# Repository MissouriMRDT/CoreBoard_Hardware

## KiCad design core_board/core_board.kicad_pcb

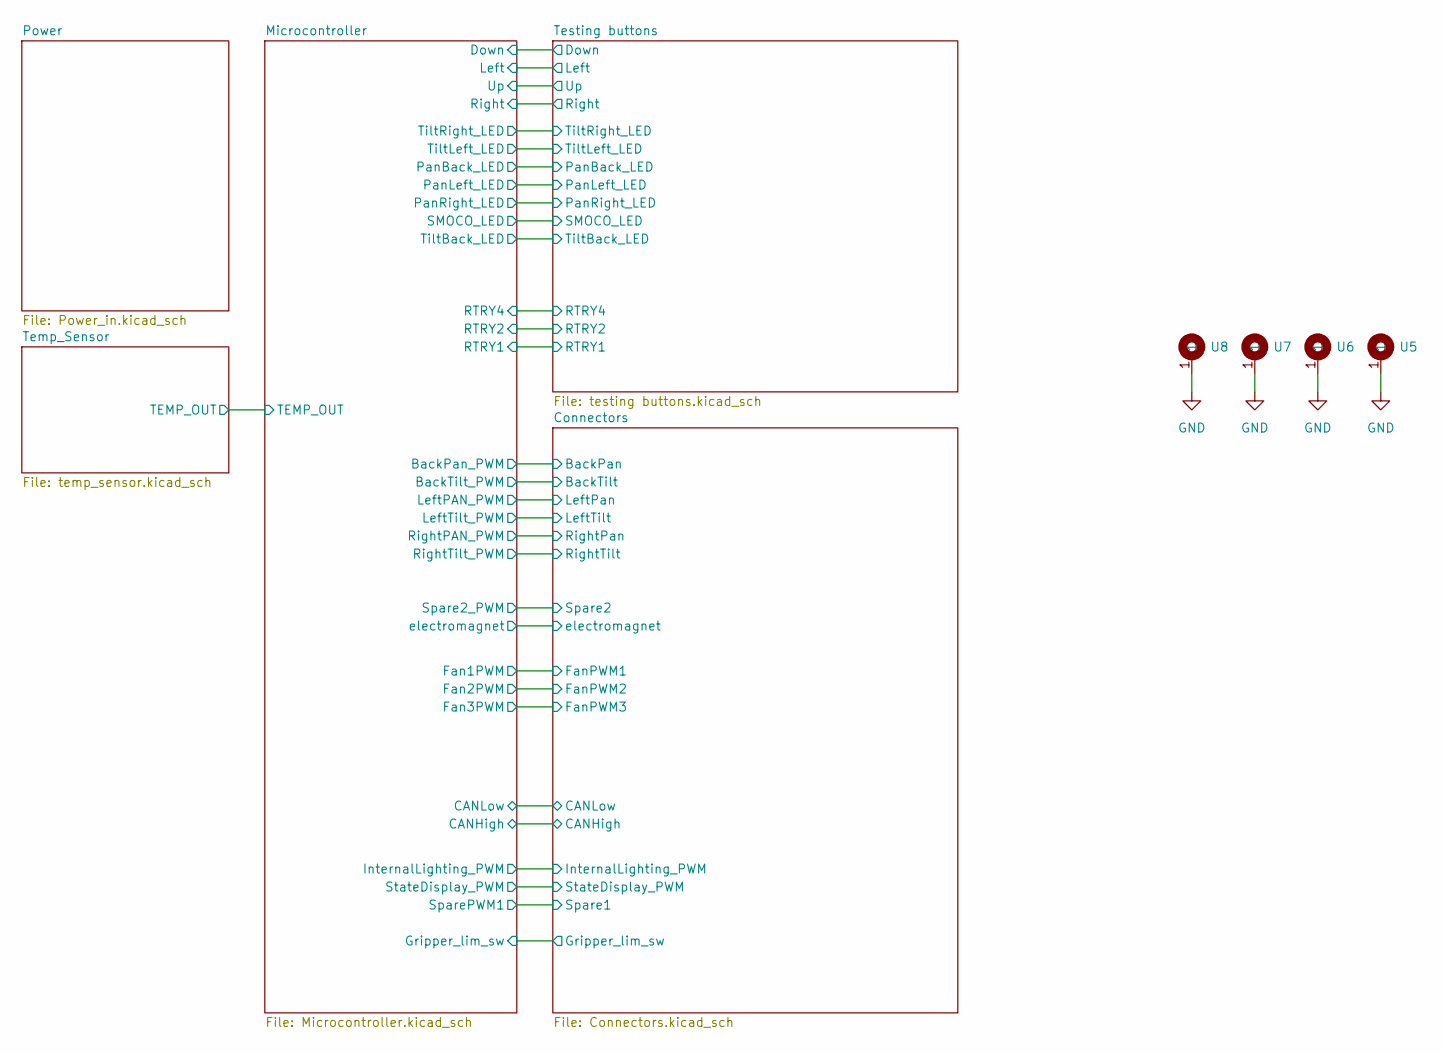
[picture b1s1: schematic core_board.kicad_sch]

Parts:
U5, U6, U7, U8: 4_40_Hole_Pad_Via

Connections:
GND: U5.1 (1_1), U6.1 (1_1), U7.1 (1_1), U8.1 (1_1); also elsewhere on the board

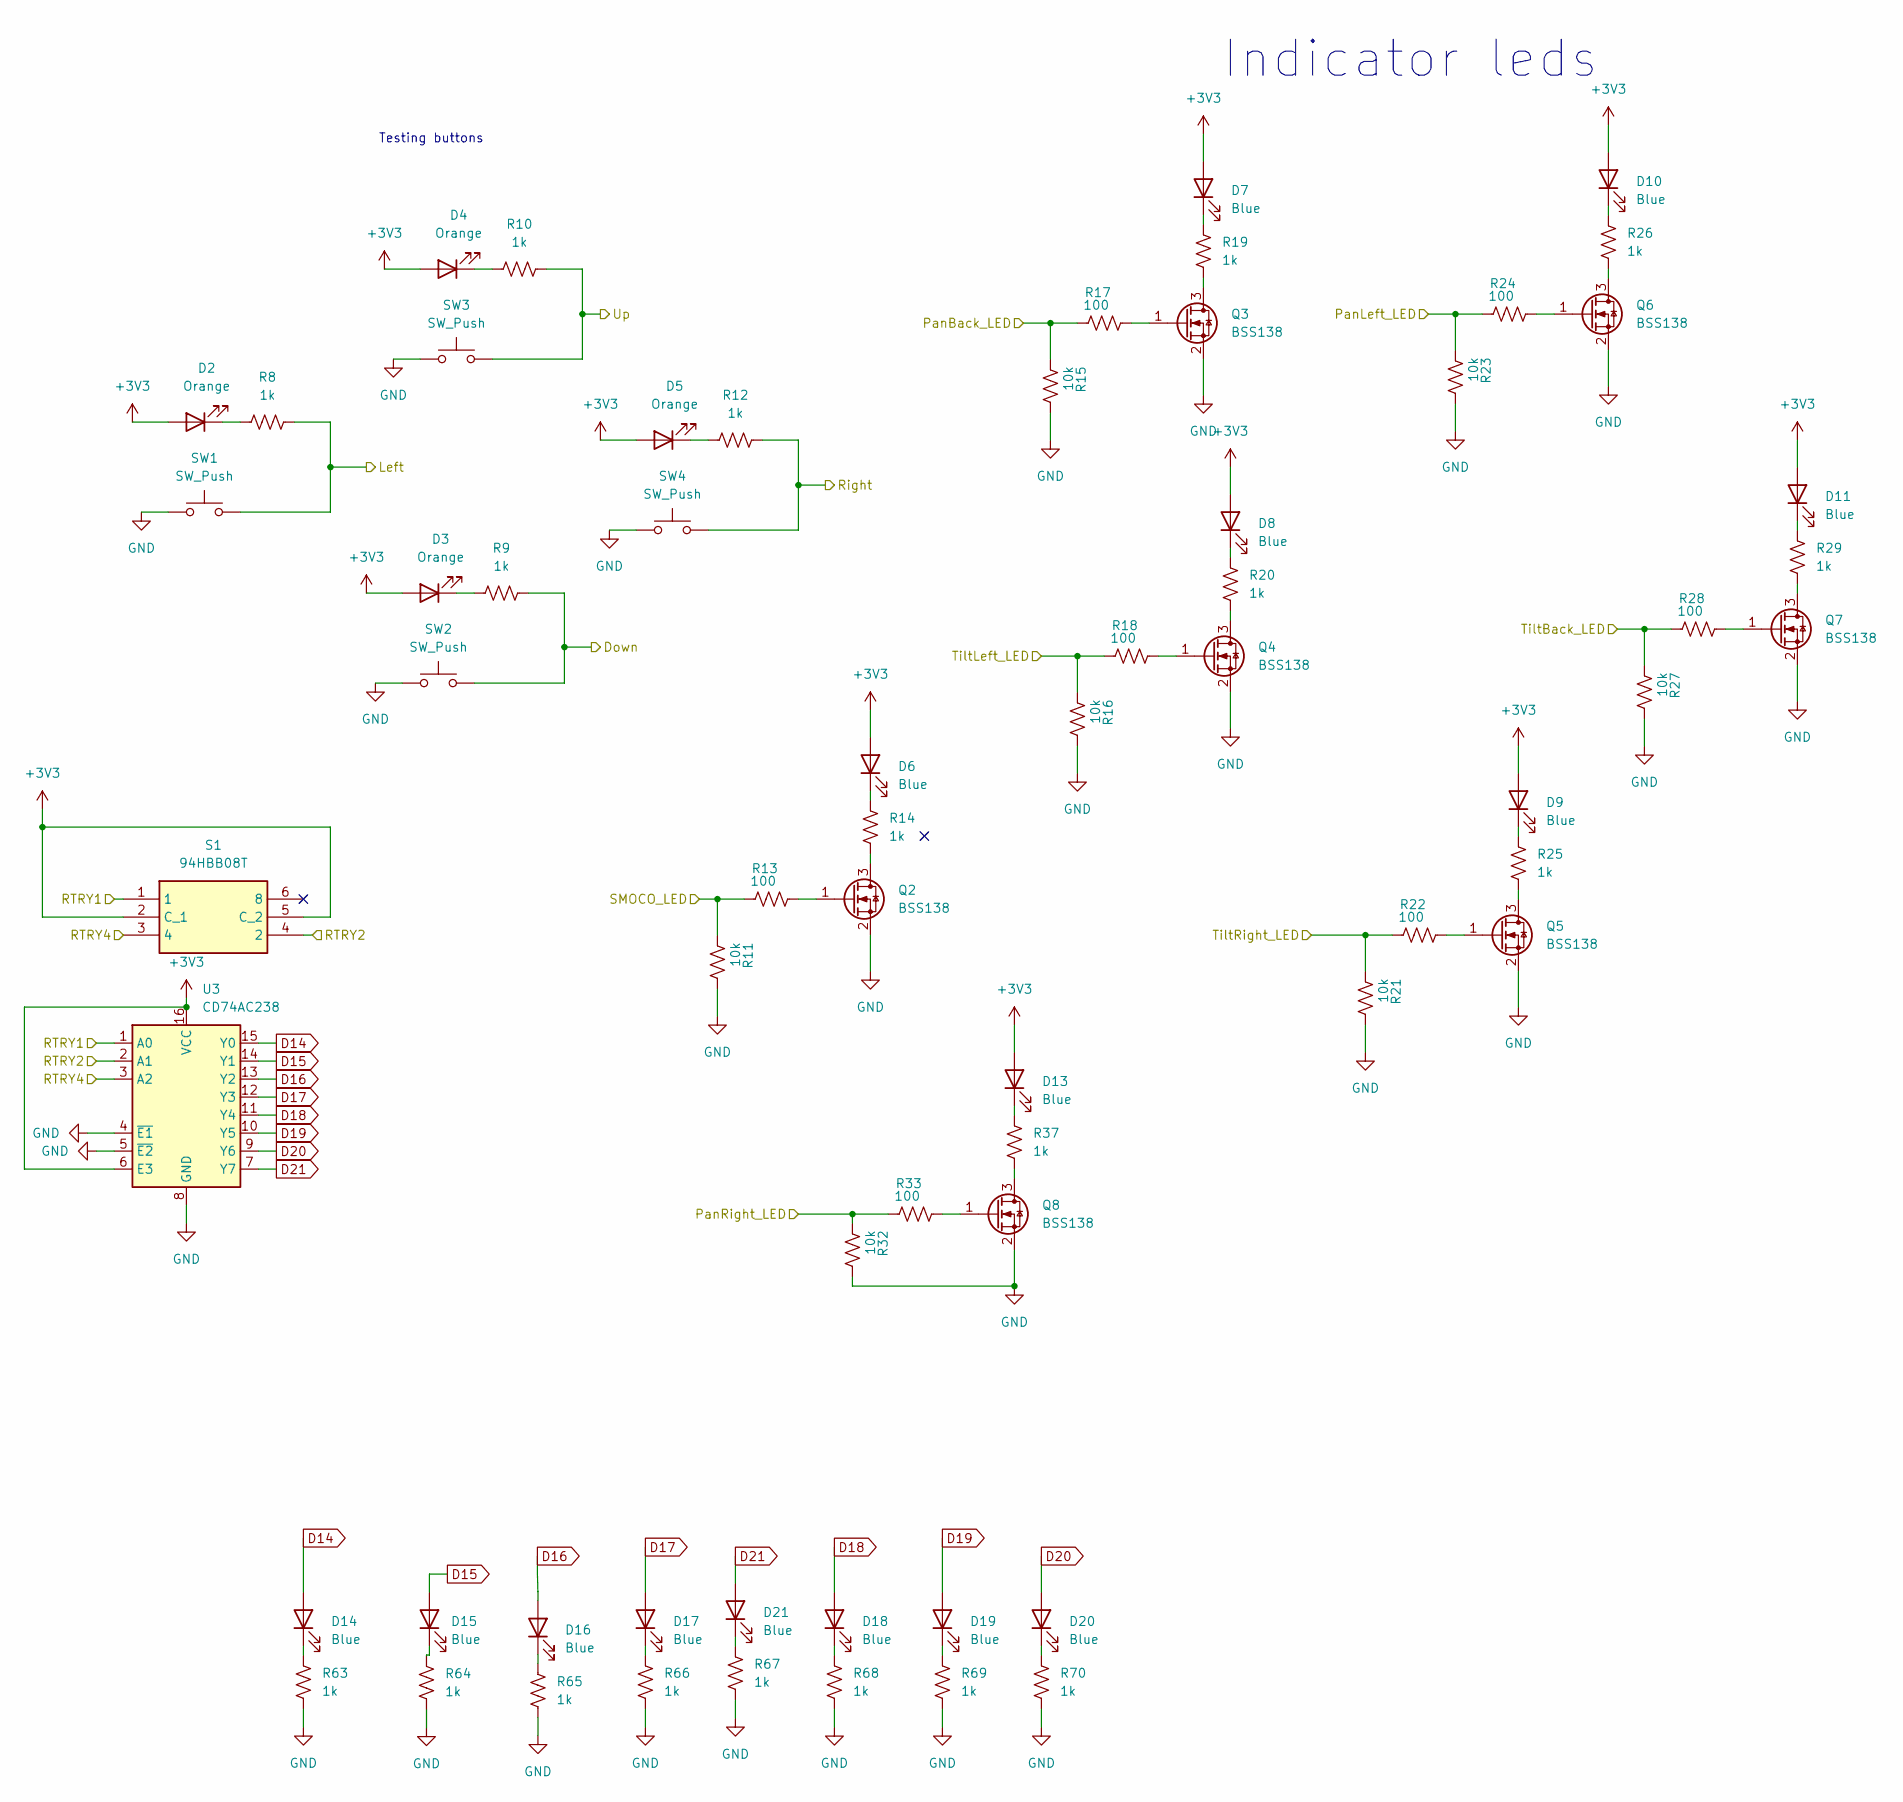
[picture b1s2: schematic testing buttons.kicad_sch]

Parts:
D2, D3, D4, D5: Orange; LED_0603_1608Metric_Pad1.05x0.95mm_HandSolder
D6, D7, D8, D9, D10, D11, D13, D14, D15, D16, D17, D18, D19, D20, D21: Blue; LED_0603_1608Metric_Pad1.05x0.95mm_HandSolder
Q2, Q3, Q4, Q5, Q6, Q7, Q8: BSS138; SOT-23
R8, R9, R10, R12, R14, R19, R20, R25, R26, R29, R37, R63, R64, R65, R66, R67, R68, R69, R70: 1k; R_0603_1608Metric_Pad0.98x0.95mm_HandSolder
R11, R15, R16, R21, R23, R27, R32: 10k; R_0603_1608Metric_Pad0.98x0.95mm_HandSolder
R13, R17, R18, R22, R24, R28, R33: 100; R_0603_1608Metric_Pad0.98x0.95mm_HandSolder
S1: 94HBB08T; DIPS762W56P254L991H597Q6N; Manufacturer_Part_Number 94HBB08T; Mouser Part Number 706-94HBB08T
SW1, SW2, SW3, SW4: SW_Push; SW_SPST_TL3305A
U3: CD74AC238; TSSOP-16_4.4x5mm_P0.65mm

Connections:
+3V3: D2.2 (A), D3.2 (A), D4.2 (A), D5.2 (A), D6.2 (A), D7.2 (A), D8.2 (A), D9.2 (A), D10.2 (A), D11.2 (A), D13.2 (A), S1.2 (C_1), S1.5 (C_2), U3.6 (E3), U3.16 (VCC); also elsewhere on the board
/Microcontroller/Down: R9.1, SW2.2; also elsewhere on the board
/Microcontroller/Left: R8.1, SW1.2; also elsewhere on the board
/Microcontroller/PanBack_LED: R15.1, R17.1; also elsewhere on the board
/Microcontroller/PanLeft_LED: R23.1, R24.1; also elsewhere on the board
/Microcontroller/PanRight_LED: R32.1, R33.1; also elsewhere on the board
/Microcontroller/RTRY1: S1.1, U3.1 (A0); also elsewhere on the board
/Microcontroller/RTRY2: S1.4 (2), U3.2 (A1); also elsewhere on the board
/Microcontroller/RTRY4: S1.3 (4), U3.3 (A2); also elsewhere on the board
/Microcontroller/Right: R12.1, SW4.2; also elsewhere on the board
/Microcontroller/SMOCO_LED: R11.1, R13.1; also elsewhere on the board
/Microcontroller/TiltBack_LED: R27.1, R28.1; also elsewhere on the board
/Microcontroller/TiltLeft_LED: R16.1, R18.1; also elsewhere on the board
/Microcontroller/TiltRight_LED: R21.1, R22.1; also elsewhere on the board
/Microcontroller/Up: R10.1, SW3.2; also elsewhere on the board
D14: D14.2 (A), U3.15 (Y0)
D15: D15.2 (A), U3.14 (Y1)
D16: D16.2 (A), U3.13 (Y2)
D17: D17.2 (A), U3.12 (Y3)
D18: D18.2 (A), U3.11 (Y4)
D19: D19.2 (A), U3.10 (Y5)
D20: D20.2 (A), U3.9 (Y6)
D21: D21.2 (A), U3.7 (Y7)
GND: Q2.2 (S), Q3.2 (S), Q4.2 (S), Q5.2 (S), Q6.2 (S), Q7.2 (S), Q8.2 (S), R11.2, R15.2, R16.2, R21.2, R23.2, R27.2, R32.2, R63.2, R64.2, R65.2, R66.2, R67.2, R68.2, R69.2, R70.2, SW1.1, SW2.1, SW3.1, SW4.1, U3.4 (~E1), U3.5 (~E2), U3.8 (GND); also elsewhere on the board
unnamed: D2.1 (K), R8.2
unnamed: D3.1 (K), R9.2
unnamed: D4.1 (K), R10.2
unnamed: D5.1 (K), R12.2
unnamed: D6.1 (K), R14.1
unnamed: D7.1 (K), R19.1
unnamed: D8.1 (K), R20.1
unnamed: D9.1 (K), R25.1
unnamed: D10.1 (K), R26.1
unnamed: D11.1 (K), R29.1
unnamed: D13.1 (K), R37.1
unnamed: D14.1 (K), R63.1
unnamed: D15.1 (K), R64.1
unnamed: D16.1 (K), R65.1
unnamed: D17.1 (K), R66.1
unnamed: D18.1 (K), R68.1
unnamed: D19.1 (K), R69.1
unnamed: D20.1 (K), R70.1
unnamed: D21.1 (K), R67.1
unnamed: Q2.3 (D), R14.2
unnamed: Q2.1 (G), R13.2
unnamed: Q3.3 (D), R19.2
unnamed: Q3.1 (G), R17.2
unnamed: Q4.3 (D), R20.2
unnamed: Q4.1 (G), R18.2
unnamed: Q5.3 (D), R25.2
unnamed: Q5.1 (G), R22.2
unnamed: Q6.3 (D), R26.2
unnamed: Q6.1 (G), R24.2
unnamed: Q7.3 (D), R29.2
unnamed: Q7.1 (G), R28.2
unnamed: Q8.3 (D), R37.2
unnamed: Q8.1 (G), R33.2

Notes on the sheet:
Indicator leds
Testing buttons

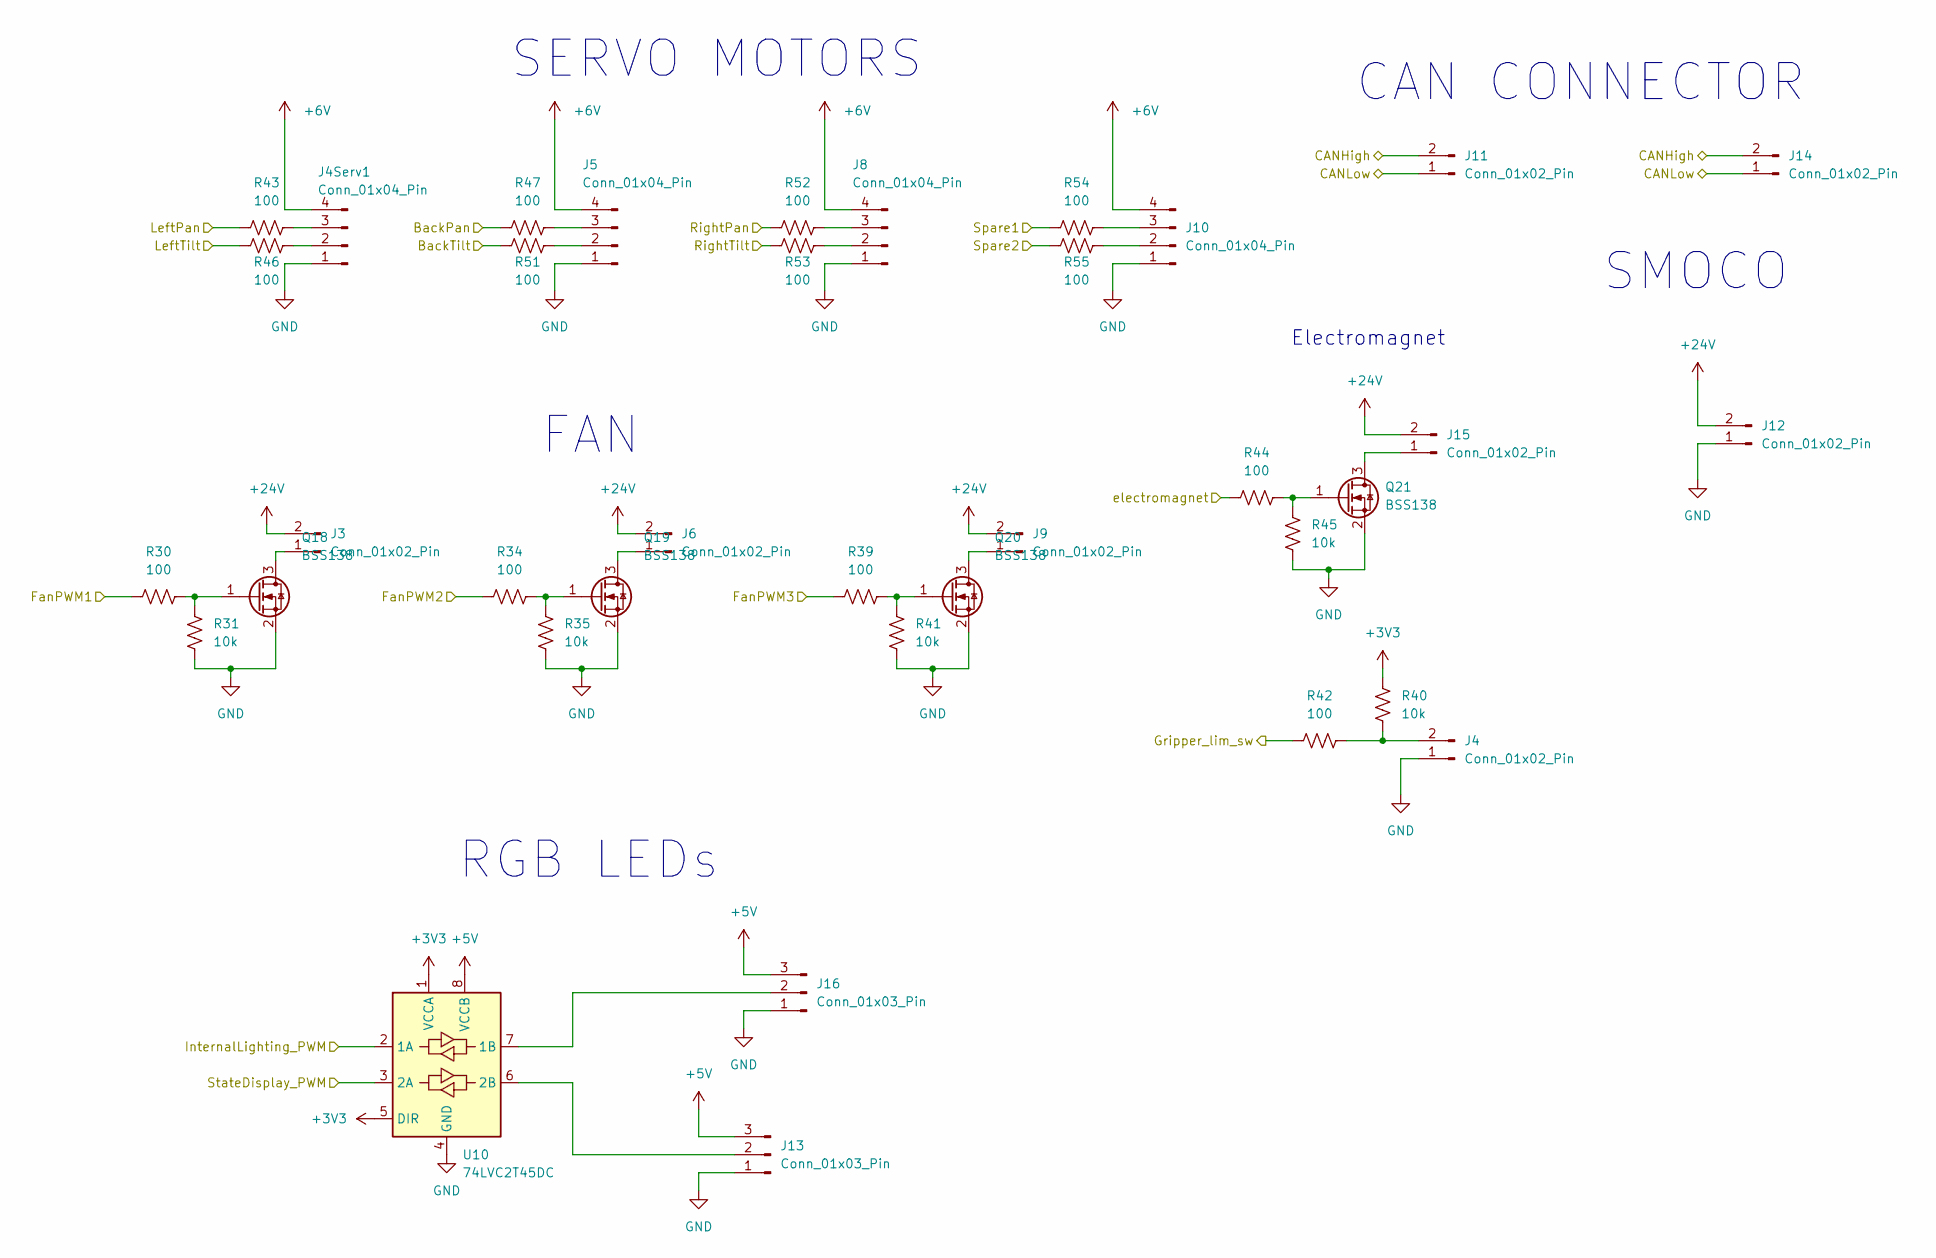
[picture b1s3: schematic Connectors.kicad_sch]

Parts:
J3, J4, J6, J9, J11, J14, J15: Conn_01x02_Pin; JST_PH_B2B-PH-K_1x02_P2.00mm_Vertical
J4Serv1, J5, J8, J10: Conn_01x04_Pin; JST_PH_B4B-PH-K_1x04_P2.00mm_Vertical
J12: Conn_01x02_Pin; MOLEX_MegaFit_02_Vertical
J13, J16: Conn_01x03_Pin; JST_PH_B3B-PH-K_1x03_P2.00mm_Vertical
Q18, Q19, Q20, Q21: BSS138; SOT-23
R30, R34, R39, R42, R43, R44, R46, R47, R51, R52, R53, R54, R55: 100; R_0603_1608Metric_Pad0.98x0.95mm_HandSolder
R31, R35, R40, R41, R45: 10k; R_0603_1608Metric_Pad0.98x0.95mm_HandSolder
U10: 74LVC2T45DC; VSSOP-8_2.3x2mm_P0.5mm

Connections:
+3V3: R40.1, U10.1 (VCCA), U10.5 (DIR); also elsewhere on the board
+5V: J13.3, J16.3, U10.8 (VCCB); also elsewhere on the board
+6V: J4Serv1.4, J5.4, J8.4, J10.4; also elsewhere on the board
+24V: J3.2, J6.2, J9.2, J12.2, J15.2; also elsewhere on the board
/Connectors/BackPan: R47.1; also elsewhere on the board
/Connectors/BackTilt: R51.1; also elsewhere on the board
/Connectors/CANHigh: J11.2, J14.2; also elsewhere on the board
/Connectors/CANLow: J11.1, J14.1; also elsewhere on the board
/Connectors/FanPWM1: R30.1; also elsewhere on the board
/Connectors/FanPWM2: R34.1; also elsewhere on the board
/Connectors/FanPWM3: R39.1; also elsewhere on the board
/Connectors/Gripper_lim_sw: R42.1; also elsewhere on the board
/Connectors/InternalLighting_PWM: U10.2 (1A); also elsewhere on the board
/Connectors/LeftPan: R43.1; also elsewhere on the board
/Connectors/LeftTilt: R46.1; also elsewhere on the board
/Connectors/RightPan: R52.1; also elsewhere on the board
/Connectors/RightTilt: R53.1; also elsewhere on the board
/Connectors/Spare1: R54.1; also elsewhere on the board
/Connectors/Spare2: R55.1; also elsewhere on the board
/Connectors/StateDisplay_PWM: U10.3 (2A); also elsewhere on the board
/Connectors/electromagnet: R44.1; also elsewhere on the board
GND: J4.1, J4Serv1.1, J5.1, J8.1, J10.1, J12.1, J13.1, J16.1, Q18.2 (S), Q19.2 (S), Q20.2 (S), Q21.2 (S), R31.1, R35.1, R41.1, R45.1, U10.4 (GND); also elsewhere on the board
unnamed: J3.1, Q18.3 (D)
unnamed: J4.2, R40.2, R42.2
unnamed: J4Serv1.2, R46.2
unnamed: J4Serv1.3, R43.2
unnamed: J5.2, R51.2
unnamed: J5.3, R47.2
unnamed: J6.1, Q19.3 (D)
unnamed: J8.2, R53.2
unnamed: J8.3, R52.2
unnamed: J9.1, Q20.3 (D)
unnamed: J10.2, R55.2
unnamed: J10.3, R54.2
unnamed: J13.2, U10.6 (2B)
unnamed: J15.1, Q21.3 (D)
unnamed: J16.2, U10.7 (1B)
unnamed: Q18.1 (G), R30.2, R31.2
unnamed: Q19.1 (G), R34.2, R35.2
unnamed: Q20.1 (G), R39.2, R41.2
unnamed: Q21.1 (G), R44.2, R45.2

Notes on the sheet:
SMOCO
Electromagnet
FAN
RGB LEDs
SERVO MOTORS
CAN CONNECTOR

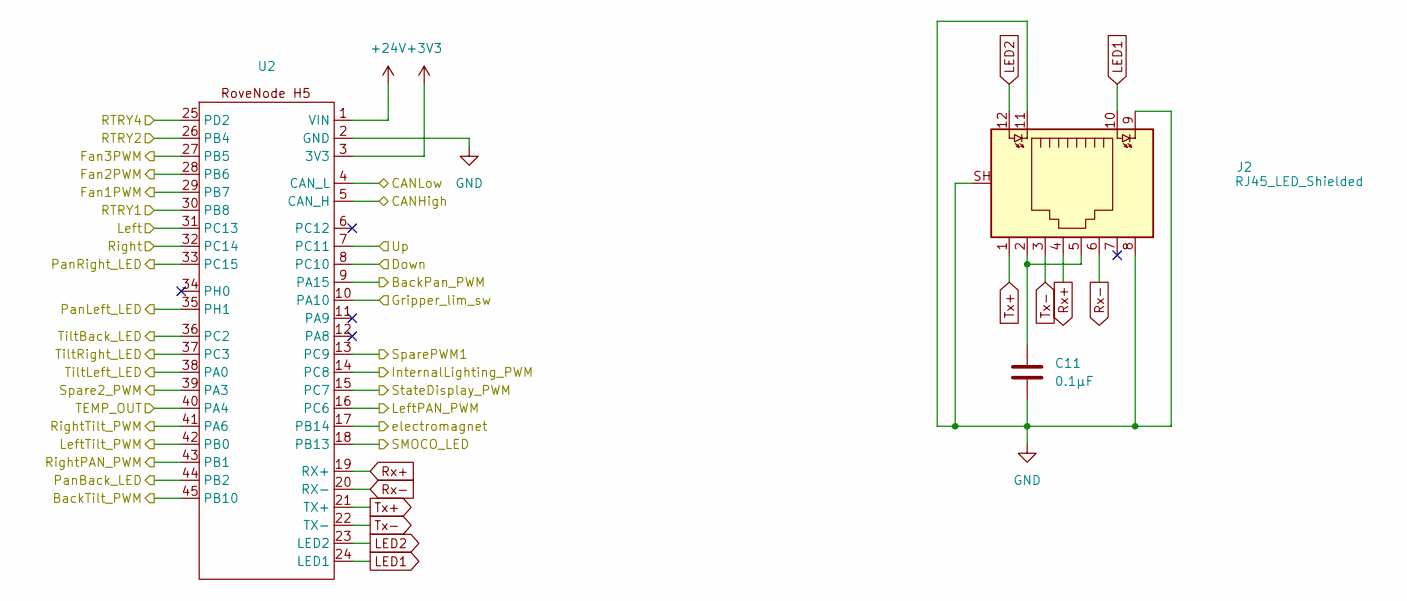
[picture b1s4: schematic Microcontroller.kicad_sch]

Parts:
C11: 0.1µF; C_0603_1608Metric_Pad1.08x0.95mm_HandSolder
J2: RJ45_LED_Shielded; RJ45_Teensy
U2: RoveNode_H5

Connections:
+3V3: U2.3 (3V3); also elsewhere on the board
+24V: U2.1 (VIN); also elsewhere on the board
/Connectors/BackPan: U2.9 (PA15); also elsewhere on the board
/Connectors/BackTilt: U2.45 (PB10); also elsewhere on the board
/Connectors/CANHigh: U2.5 (CAN_H); also elsewhere on the board
/Connectors/CANLow: U2.4 (CAN_L); also elsewhere on the board
/Connectors/FanPWM1: U2.29 (PB7); also elsewhere on the board
/Connectors/FanPWM2: U2.28 (PB6); also elsewhere on the board
/Connectors/FanPWM3: U2.27 (PB5); also elsewhere on the board
/Connectors/Gripper_lim_sw: U2.10 (PA10); also elsewhere on the board
/Connectors/InternalLighting_PWM: U2.14 (PC8); also elsewhere on the board
/Connectors/LeftPan: U2.16 (PC6); also elsewhere on the board
/Connectors/LeftTilt: U2.42 (PB0); also elsewhere on the board
/Connectors/RightPan: U2.43 (PB1); also elsewhere on the board
/Connectors/RightTilt: U2.41 (PA6); also elsewhere on the board
/Connectors/Spare1: U2.13 (PC9); also elsewhere on the board
/Connectors/Spare2: U2.39 (PA3); also elsewhere on the board
/Connectors/StateDisplay_PWM: U2.15 (PC7); also elsewhere on the board
/Connectors/electromagnet: U2.17 (PB14); also elsewhere on the board
/Microcontroller/Down: U2.8 (PC10); also elsewhere on the board
/Microcontroller/Left: U2.31 (PC13); also elsewhere on the board
/Microcontroller/PanBack_LED: U2.44 (PB2); also elsewhere on the board
/Microcontroller/PanLeft_LED: U2.35 (PH1); also elsewhere on the board
/Microcontroller/PanRight_LED: U2.33 (PC15); also elsewhere on the board
/Microcontroller/RTRY1: U2.30 (PB8); also elsewhere on the board
/Microcontroller/RTRY2: U2.26 (PB4); also elsewhere on the board
/Microcontroller/RTRY4: U2.25 (PD2); also elsewhere on the board
/Microcontroller/Right: U2.32 (PC14); also elsewhere on the board
/Microcontroller/SMOCO_LED: U2.18 (PB13); also elsewhere on the board
/Microcontroller/TEMP_OUT: U2.40 (PA4); also elsewhere on the board
/Microcontroller/TiltBack_LED: U2.36 (PC2); also elsewhere on the board
/Microcontroller/TiltLeft_LED: U2.38 (PA0); also elsewhere on the board
/Microcontroller/TiltRight_LED: U2.37 (PC3); also elsewhere on the board
/Microcontroller/Up: U2.7 (PC11); also elsewhere on the board
GND: C11.2, J2.8, J2.9, J2.11, J2.SH, U2.2 (GND); also elsewhere on the board
LED1: J2.10, U2.24 (LED1)
LED2: J2.12, U2.23 (LED2)
unnamed: C11.1, J2.2, J2.5
Rx+: J2.4, U2.19 (RX+)
Rx-: J2.6, U2.20 (RX-)
Tx+: J2.1, U2.21 (TX+)
Tx-: J2.3, U2.22 (TX-)

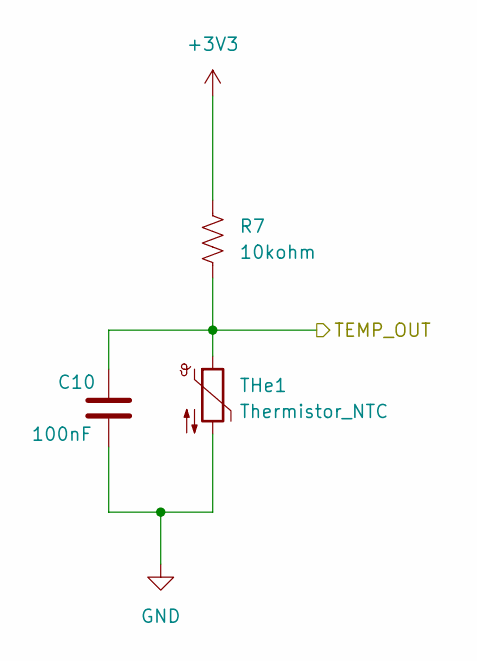
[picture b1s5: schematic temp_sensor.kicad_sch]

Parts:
C10: 100nF; C_0603_1608Metric_Pad1.08x0.95mm_HandSolder
R7: 10kohm; R_0603_1608Metric_Pad0.98x0.95mm_HandSolder
THe1: Thermistor_NTC; R_0603_1608Metric_Pad0.98x0.95mm_HandSolder

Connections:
+3V3: R7.1; also elsewhere on the board
/Microcontroller/TEMP_OUT: C10.1, R7.2, THe1.1; also elsewhere on the board
GND: C10.2, THe1.2; also elsewhere on the board

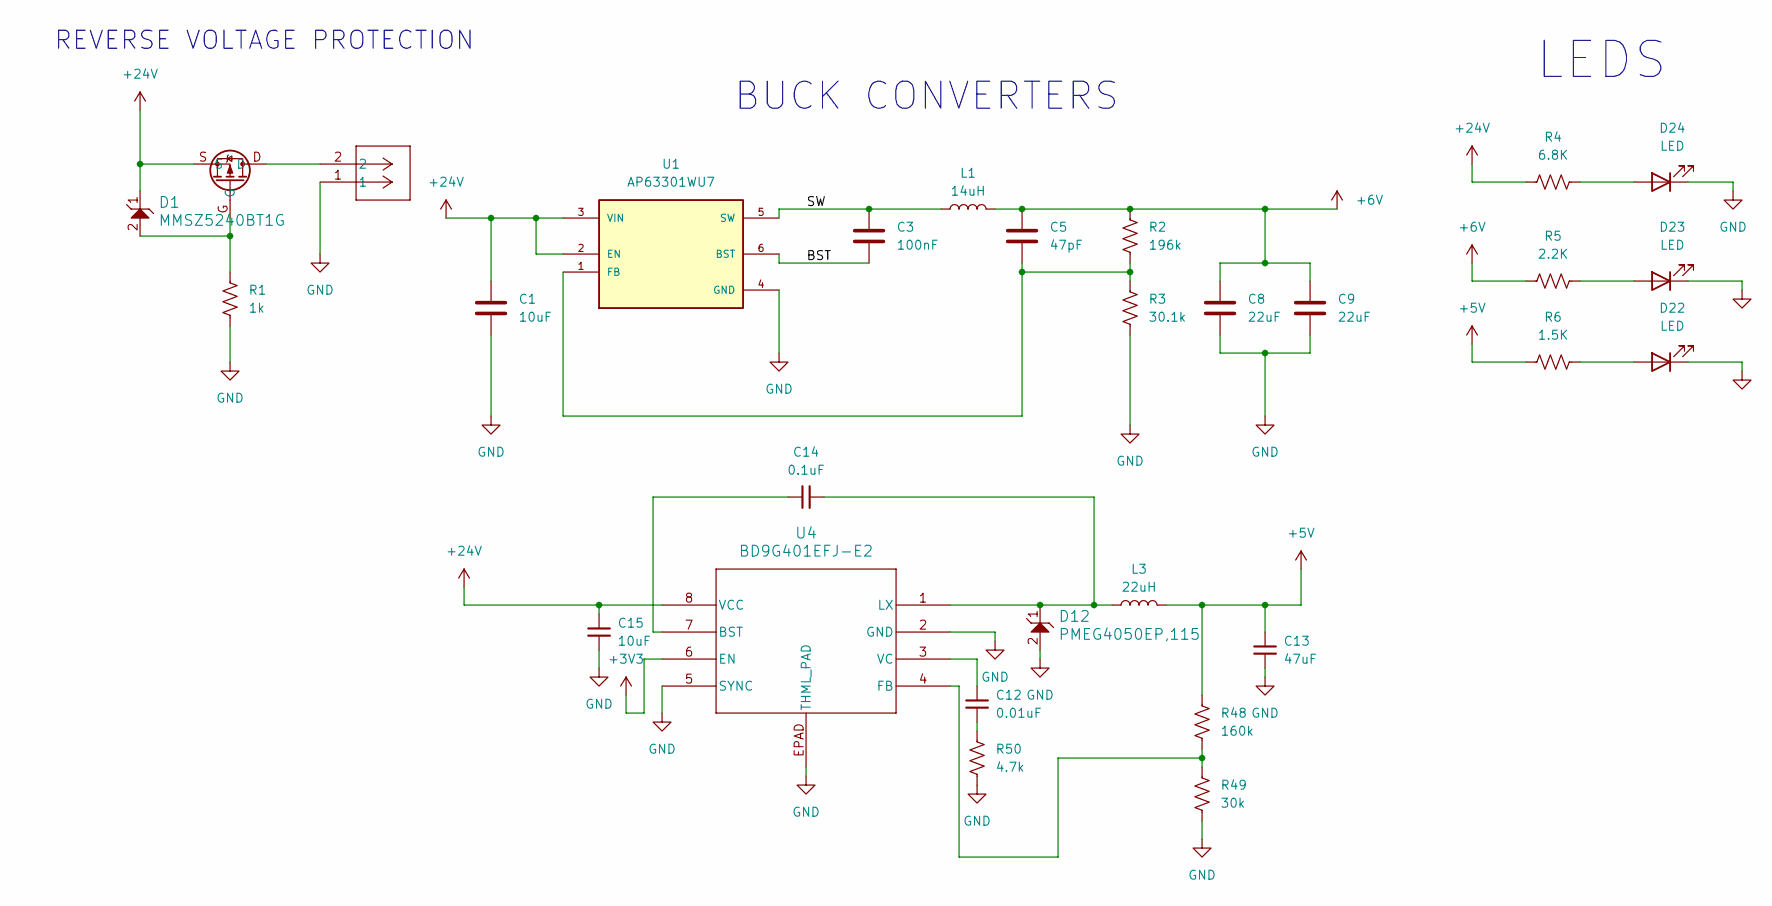
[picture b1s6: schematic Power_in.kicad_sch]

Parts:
C1, C15: 10uF; C_0603_1608Metric_Pad1.08x0.95mm_HandSolder
C3: 100nF; C_0603_1608Metric_Pad1.08x0.95mm_HandSolder
C5: 47pF; C_0603_1608Metric_Pad1.08x0.95mm_HandSolder
C8, C9: 22uF; C_0603_1608Metric_Pad1.08x0.95mm_HandSolder
C12: 0.01uF; C_0603_1608Metric_Pad1.08x0.95mm_HandSolder
C13: 47uF; C_1206_3216Metric_Pad1.33x1.80mm_HandSolder
C14: 0.1uF; C_0603_1608Metric_Pad1.08x0.95mm_HandSolder
D1: MMSZ5240BT1G; SOD-123_ONS-L
D12: PMEG4050EP,115; D_SOD-128
D22, D23, D24: LED; LED_0603_1608Metric_Pad1.05x0.95mm_HandSolder
J1: Molex_Megafit_02; MOLEX_MegaFit_02_Vertical
L1: 14uH; L_TechFuse_SL1050
L3: 22uH; IND_AMRM00101040_PUL
Q1: TPC8132_LQS
R1: 1k; R_0603_1608Metric_Pad0.98x0.95mm_HandSolder
R2: 196k; R_0603_1608Metric_Pad0.98x0.95mm_HandSolder
R3: 30.1k; R_0603_1608Metric_Pad0.98x0.95mm_HandSolder
R4: 6.8K; R_0603_1608Metric_Pad0.98x0.95mm_HandSolder
R5: 2.2K; R_0603_1608Metric_Pad0.98x0.95mm_HandSolder
R6: 1.5K; R_0603_1608Metric_Pad0.98x0.95mm_HandSolder
R48: 160k; R_0603_1608Metric_Pad0.98x0.95mm_HandSolder
R49: 30k; R_0603_1608Metric_Pad0.98x0.95mm_HandSolder
R50: 4.7k; R_0603_1608Metric_Pad0.98x0.95mm_HandSolder
U1: AP63301WU7; SOT-23-6_Handsoldering; PARTREV 1 - 2; DigiKey_Part_Number 31-AP63205QWU-7CT-ND
U4: BD9G401EFJ-E2; SOIC-8-1EP_3.9x4.9mm_P1.27mm_EP2.29x3mm

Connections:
+3V3: U4.6 (EN); also elsewhere on the board
+5V: C13.1, L3.2, R6.1, R48.1; also elsewhere on the board
+6V: C5.1, C8.1, C9.1, L1.2, R2.1, R5.1; also elsewhere on the board
+24V: C1.1, C15.1, D1.1, Q1.S, R4.1, U1.2 (EN), U1.3 (VIN), U4.8 (VCC); also elsewhere on the board
/Power/BST: C3.2, U1.6 (BST)
/Power/SW: C3.1, L1.1, U1.5 (SW)
GND: C1.2, C8.2, C9.2, C13.2, C15.2, D12.2, D22.1 (K), D23.1 (K), D24.1 (K), J1.1, R1.2, R3.2, R49.2, R50.2, U1.4 (GND), U4.2 (GND), U4.5 (SYNC), U4.EPAD (THML_PAD); also elsewhere on the board
unnamed: C12.2, R50.1
unnamed: D1.2, Q1.G, R1.1
unnamed: D22.2 (A), R6.2
unnamed: D23.2 (A), R5.2
unnamed: D24.2 (A), R4.2
unnamed: J1.2, Q1.D
unnamed: C5.2, R2.2, R3.1, U1.1 (FB)
unnamed: C14.1, U4.7 (BST)
unnamed: R48.2, R49.1, U4.4 (FB)
unnamed: C14.2, D12.1, L3.1, U4.1 (LX)
unnamed: C12.1, U4.3 (VC)

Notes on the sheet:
BUCK CONVERTERS
REVERSE VOLTAGE PROTECTION
LEDS

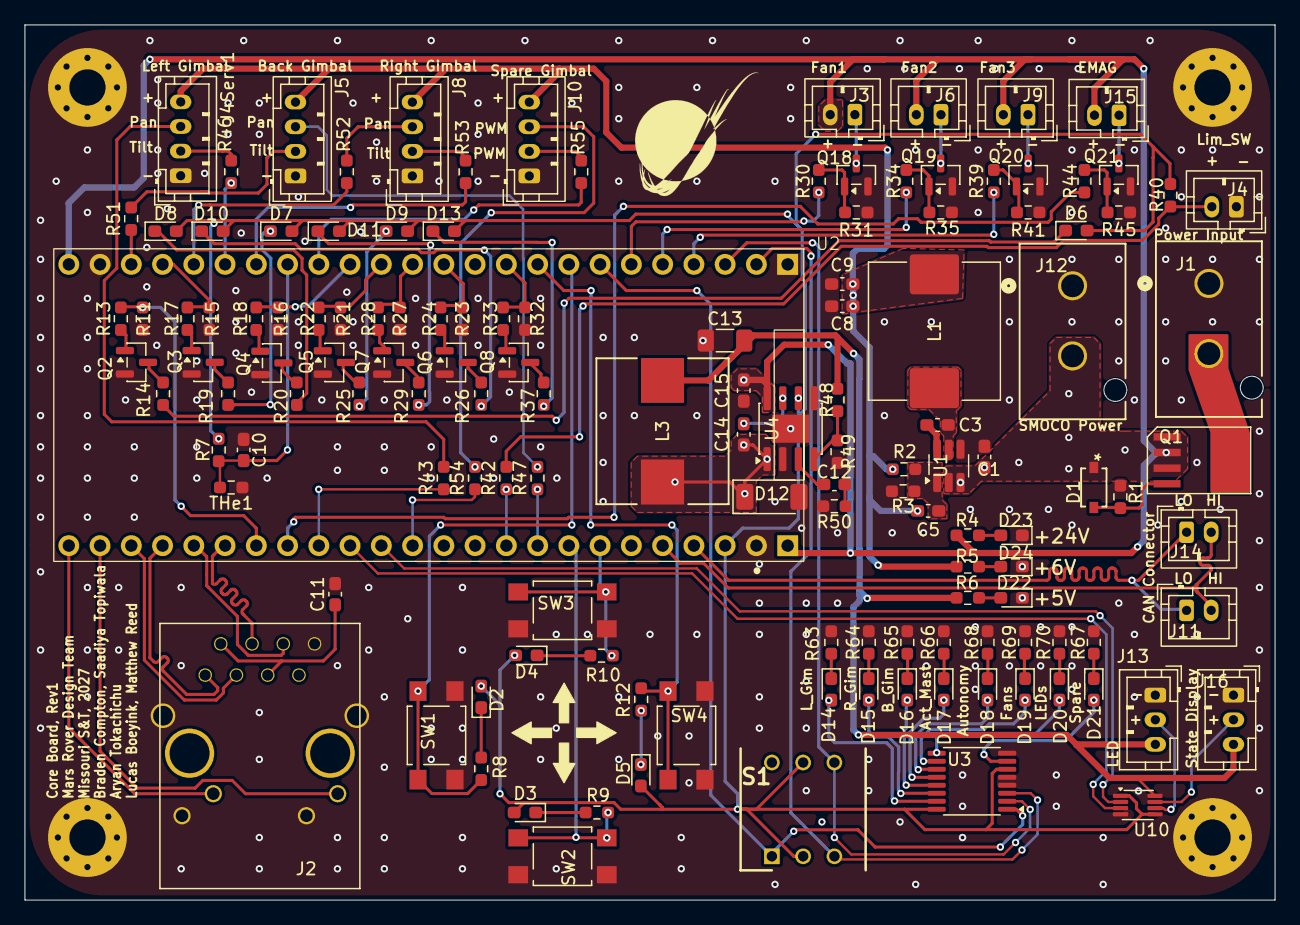
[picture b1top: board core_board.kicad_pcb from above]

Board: 4 copper layers, 101.6 x 71.1 mm, 141 parts (0 on the bottom side), 117 nets.

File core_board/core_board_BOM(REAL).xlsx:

Reference | Value | Footprint | Datasheet | Qty | Price per Component | Total:
C1,C15 | 10uF | Capacitor_SMD:C_0603_1608Metric_Pad1.08x0.95mm_HandSolder |  | 2 | ~ | ~
C3,C10 | 100nF | Capacitor_SMD:C_0603_1608Metric_Pad1.08x0.95mm_HandSolder |  | 2 | ~ | ~
C5 | 47pF | Capacitor_SMD:C_0603_1608Metric_Pad1.08x0.95mm_HandSolder |  | 1 | ~ | ~
C8,C9 | 22uF | Capacitor_SMD:C_0603_1608Metric_Pad1.08x0.95mm_HandSolder |  | 2 | ~ | ~
C11 | 0.1ÂµF | Capacitor_SMD:C_0603_1608Metric_Pad1.08x0.95mm_HandSolder |  | 1 | ~ | ~
C12 | 0.01uF | Capacitor_SMD:C_0603_1608Metric_Pad1.08x0.95mm_HandSolder |  | 1 | ~ | ~
C13 | 47uF | Capacitor_SMD:C_0603_1608Metric_Pad1.08x0.95mm_HandSolder |  | 1 | ~ | ~
C14 | 0.1uF | Capacitor_SMD:C_0603_1608Metric_Pad1.08x0.95mm_HandSolder |  | 1 | ~ | ~
D1 | MMSZ5240BT1G | LED_SMD:LED_0603_1608Metric_Pad1.05x0.95mm_HandSolder | https://www.onsemi.com/pdf/datasheet/mmsz5221bt1-d.pdf | 1 | ~ | ~
D2,D3,D4,D5 | Orange | LED_SMD:LED_0603_1608Metric_Pad1.05x0.95mm_HandSolder |  | 4 | ~ | ~
D6,D7,D8,D9,D10,D11 | Blue | LED_SMD:LED_0603_1608Metric_Pad1.05x0.95mm_HandSolder |  | 6 | ~ | ~
D12 | PMEG4050EP,115 | Diode_SMD:D_SOD-128 | https://assets.nexperia.com/documents/data-sheet/PMEG4050EP.pdf | 1 | 0.9 | 0.9
GreenLED1,GreenLED2,GreenLED3 | LED | LED_SMD:LED_0603_1608Metric_Pad1.05x0.95mm_HandSolder |  | 3 | ~ | ~
J1 | Molex_Megafit_02 | MRDT_Connectors:MOLEX_MegaFit_02_Vertical | https://www.molex.com/en-us/products/part-detail-pdf/7682500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 | 1 | ~ | ~
J2 | RJ45_LED_Shielded | MRDT_Connectors:RJ45_Teensy |  | 1 | ~ | ~
J3,J6,J9,J11,J14,J15 | Conn_01x02_Pin | Connector_JST:JST_PH_B2B-PH-K_1x02_P2.00mm_Vertical |  | 6 | ~ | ~
J4Serv1,J5,J8,J10 | Conn_01x04_Pin | Connector_JST:JST_PH_B4B-PH-K_1x04_P2.00mm_Vertical |  | 4 | ~ | ~
J12 | Conn_01x02_Pin | MRDT_Connectors:MOLEX_MegaFit_02_Vertical |  | 1 | ~ | ~
J13,J16 | Conn_01x03_Pin | Connector_JST:JST_PH_B3B-PH-K_1x03_P2.00mm_Vertical |  | 2 | ~ | ~
L1 | 14uH | Inductor_SMD:L_TechFuse_SL1050 | https://www.codaca.com/Private/pdf/CSBA1050.pdf | 1 | 1.92 | 1.92
L3 | 22uH | AMRM00101040220MA1:IND_AMRM00101040_PUL | https://www.digikey.com/en/products/detail/pulse-electronics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 | 1 | 0.43 | 0.43
Q1 | TPC8132_LQS | MRDT_Devices:TPC8132_LQS |  | 1 | ~ | ~
Q2,Q3,Q4,Q5,Q6,Q7,Q18,Q19,Q20,Q21 | BSS138 | Package_TO_SOT_SMD:SOT-23 | https://www.onsemi.com/pub/Collateral/BSS138-D.PDF | 10 | ~ | ~
R1,R14,R19,R20,R25,R26,R29 | 1k | Resistor_SMD:R_0603_1608Metric_Pad0.98x0.95mm_HandSolder |  | 7 | ~ | ~
R2 | 252K | Resistor_SMD:R_0603_1608Metric_Pad0.98x0.95mm_HandSolder |  | 1 | ~ | ~
R3 | 30.1k | Resistor_SMD:R_0603_1608Metric_Pad0.98x0.95mm_HandSolder |  | 1 | ~ | ~
R4 | 6.8K | Resistor_SMD:R_0603_1608Metric_Pad0.98x0.95mm_HandSolder |  | 1 | ~ | ~
R5 | 2.2K | Resistor_SMD:R_0603_1608Metric_Pad0.98x0.95mm_HandSolder |  | 1 | ~ | ~
R6 | 1.5K | Resistor_SMD:R_0603_1608Metric_Pad0.98x0.95mm_HandSolder |  | 1 | ~ | ~
R7 | 10kohm | Resistor_SMD:R_0603_1608Metric_Pad0.98x0.95mm_HandSolder |  | 1 | ~ | ~
R8,R9,R10,R12 | 2.2k | Resistor_SMD:R_0603_1608Metric_Pad0.98x0.95mm_HandSolder |  | 4 | ~ | ~
R11,R15,R16,R21,R23,R27,R31,R35,R41,R45 | 10k | Resistor_SMD:R_0603_1608Metric_Pad0.98x0.95mm_HandSolder |  | 10 | ~ | ~
R13,R17,R18,R22,R24,R28,R30,R34,R39,R44 | 100 | Resistor_SMD:R_0603_1608Metric_Pad0.98x0.95mm_HandSolder |  | 10 | ~ | ~
R32Serv1,R36,R38,R42 | 220 | Resistor_SMD:R_0603_1608Metric_Pad0.98x0.95mm_HandSolder |  | 4 | ~ | ~
R48 | 160k | Resistor_SMD:R_0603_1608Metric_Pad0.98x0.95mm_HandSolder |  | 1 | ~ | ~
R49 | 30k | Resistor_SMD:R_0603_1608Metric_Pad0.98x0.95mm_HandSolder |  | 1 | ~ | ~
R50 | 4.7k | Resistor_SMD:R_0603_1608Metric_Pad0.98x0.95mm_HandSolder |  | 1 | ~ | ~
S1 | 94HBB08T | 94HBBBO6T:DIPS762W56P254L991H597Q6N | https://datasheet.datasheetarchive.com/originals/distributor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 | 1 | 5.61 | 5.61
SW1,SW2,SW3,SW4 | SW_Push | MRDT_Switches:SW_SPST_TL3305A |  | 4 | ~ | ~
THe1 | Thermistor_NTC | Resistor_SMD:R_1206_3216Metric_Pad1.30x1.75mm_HandSolder | https://www.tdk-electronics.tdk.com/inf/50/db/ntc/NTC_SMD_St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 | 1 | 0.12 | 0.12
U1 | AP63301WU7 | Package_TO_SOT_SMD:SOT-23-6_Handsoldering | https://www.diodes.com/assets/Datasheets/AP63200Q_AP63201Q_A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 | 1 | 0.96 | 0.96
U3 |  | MRDT_Shields:RoveNode_H5 |  | 1 | 25 | 25
U4 | BD9G401EFJ-E2 | Package_SO:SOIC-8-1EP_3.9x4.9mm_P1.27mm_EP2.29x3mm | https://fscdn.rohm.com/en/products/databook/datasheet/ic/pow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 | 1 | 1.55 | 1.55
U5,U6,U7,U8 |  | MRDT_Drill_Holes:4_40_Hole_Pad_Via |  | 4 | ~ | ~
Standard Components: | ~ | ~ | ~ | ~ | ~ | 15
 |  |  |  |  | Total: | 51.489999999999995
